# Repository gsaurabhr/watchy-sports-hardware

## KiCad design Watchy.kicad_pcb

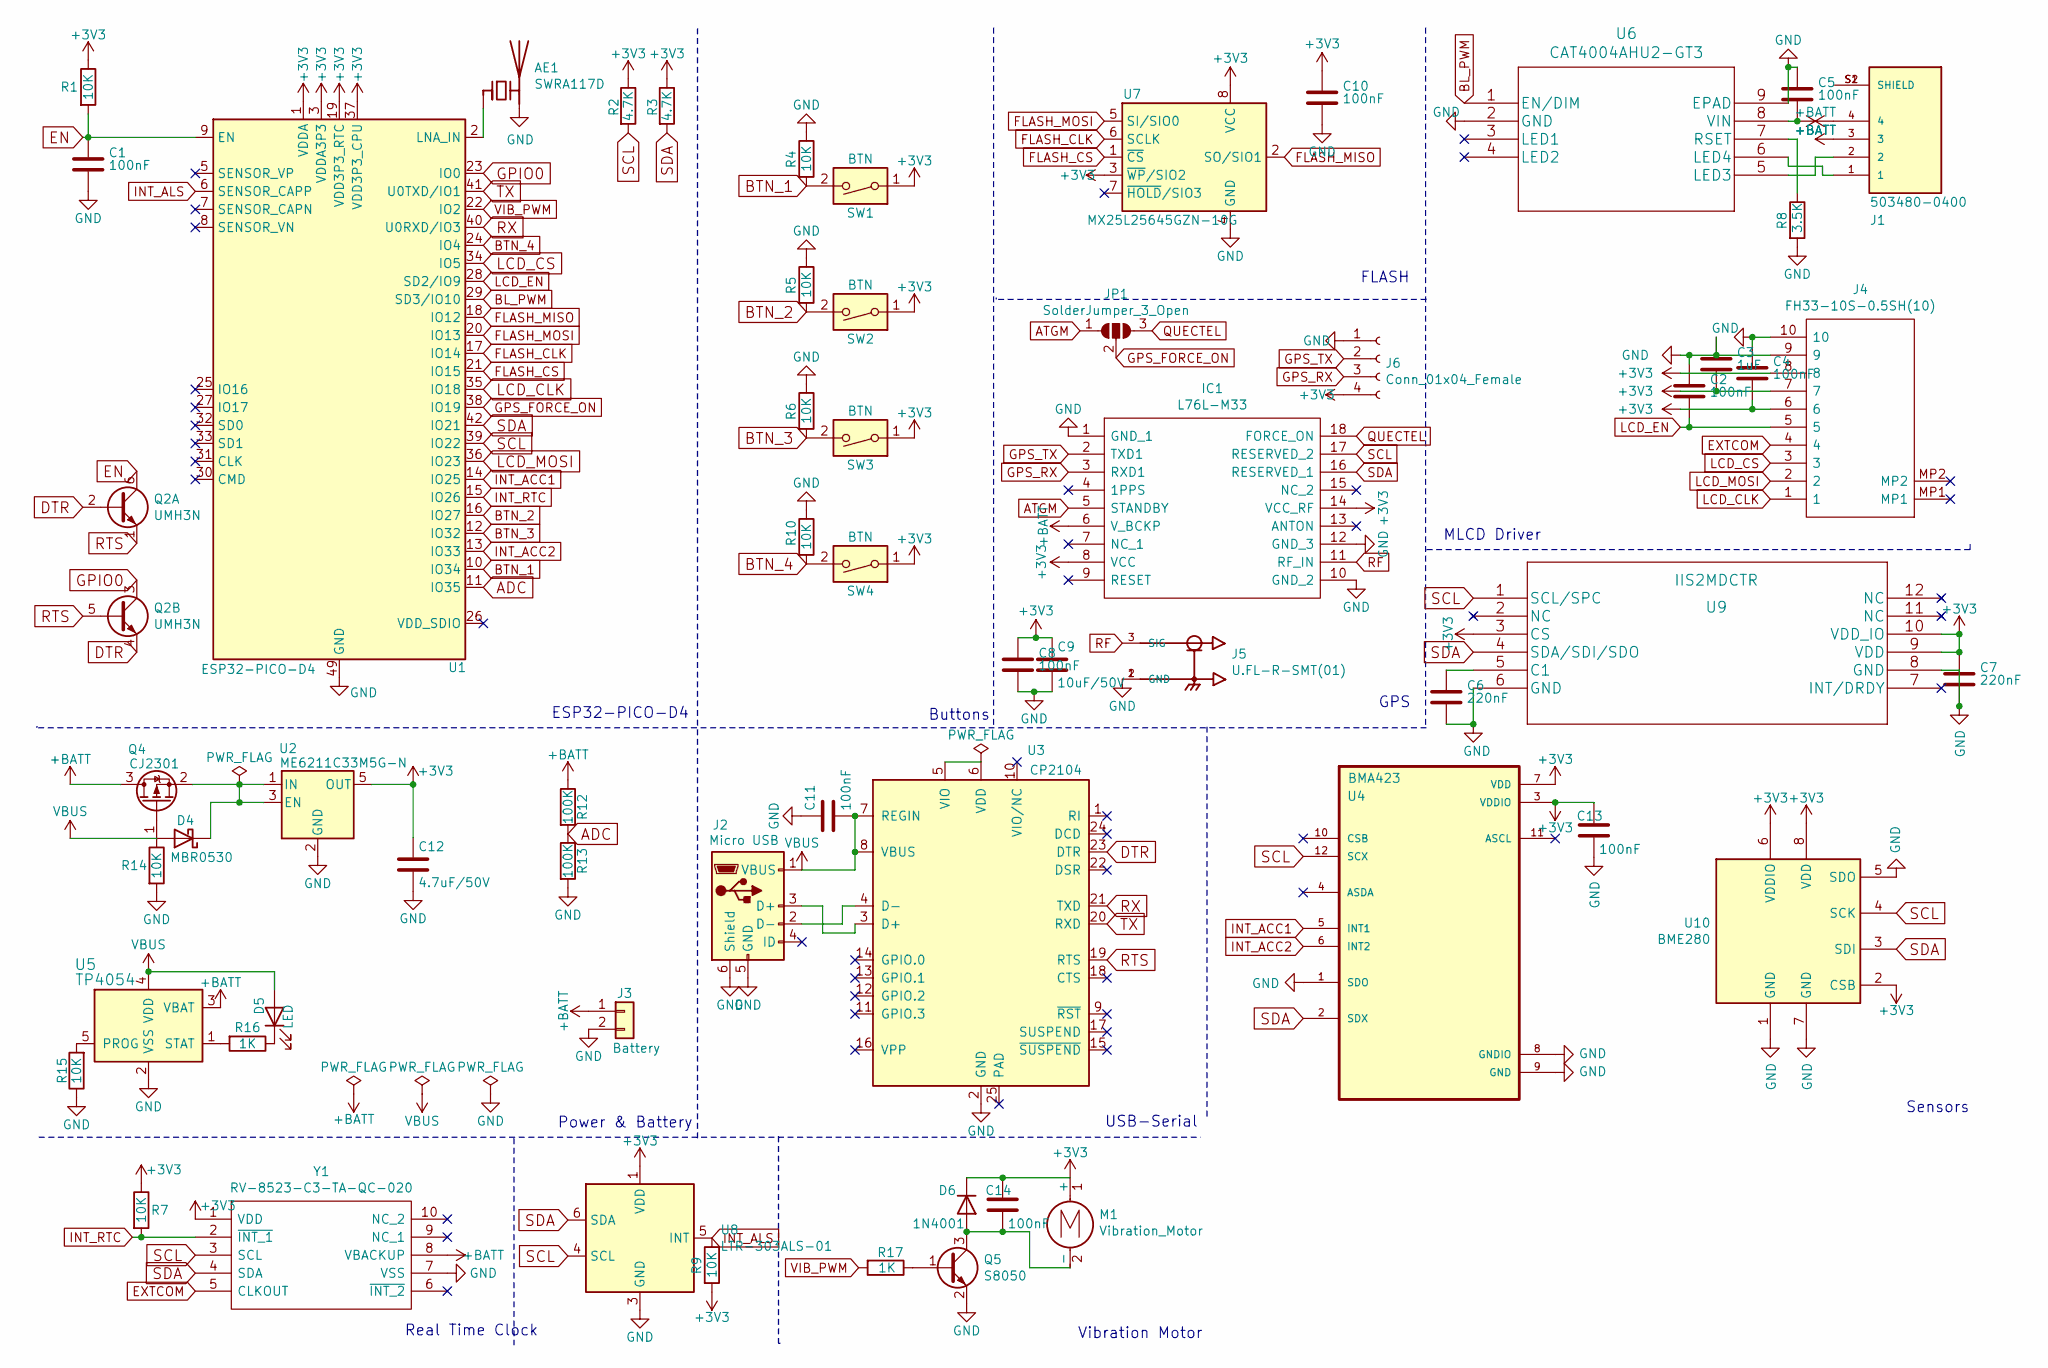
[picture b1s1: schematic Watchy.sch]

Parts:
AE1: SWRA117D
C1, C2, C4, C5, C8, C10, C11, C13, C14: 100nF; C_0603_1608Metric
C3: 1uF; C_0603_1608Metric
C6, C7: 220nF; C_0603_1608Metric
C9: 10uF/50V; C_0805_2012Metric
C12: 4.7uF/50V; C_0805
D4: MBR0530; D_SOD-123; MPN MBR0530; LCSC C77336
D5: LED; LED_0603; MPN LTST-C190KRKT; LCSC C2286
D6: 1N4001; D_SOD-123F; MPN 1N4001; LCSC C433392
IC1: L76L-M33; L76; Manufacturer_Part_Number L76L-M33; Mouser Part Number 277-L76-M33
J1: 503480-0400; MOLEX_503480-0400; MPN 503480-0400; LCSC C563965
J2: Micro USB; USB_Micro-B; MPN U-F-M5DD-Y-L; LCSC C91146
J3: Battery; 1.25T-2PWT (Molex 532610271); MPN 532610271; LCSC C189700
J4: FH33-10S-0.5SH(10); FH3310S05SH10; MPN FH33-10S-0.5SH(10); Mouser Part Number 798-FH3310S0.5SH10
J5: U.FL-R-SMT(01); HRS_U.FL-R-SMT(01); MPN U.FL-R-SMT(01); LCSC C88374
J6: Conn_01x04_Female; PinSocket_1x04_P1.00mm_Vertical
JP1: SolderJumper_3_Open; SolderJumper-3_P1.3mm_Open_Pad1.0x1.5mm
M1: Vibration_Motor; Motor_Header
Q2: UMH3N; SOT-363_SC-70-6; MPN UMH3N; LCSC C62892
Q4: CJ2301; SOT-23; MPN CJ2301; LCSC C8547
Q5: S8050; SOT-23; MPN S8050; LCSC C2146
R1, R4, R5, R6, R7, R9, R10, R14, R15: 10K; R_0402_1005Metric
R2, R3: 4.7K; R_0402_1005Metric
R8: 3.5K; R_0402_1005Metric
R12, R13: 100K; R_0402_1005Metric
R16, R17: 1K; R_0402_1005Metric
SW1, SW2, SW3, SW4: BTN; K2-1114SA-A4SW-06; MPN K2-1114SA-A4SW-06; LCSC C136662
U1: ESP32-PICO-D4; QFN-48-1EP_7x7mm_Pitch0.5mm; MPN ESP32-PICO-D4; LCSC C193707
U2: ME6211C33M5G-N; SOT-23-5; MPN ME6211C33M5G-N; LCSC C82942
U3: CP2104; QFN-24-1EP_4x4mm_Pitch0.5mm; MPN CP2104-F03-GM; LCSC C430013
U4: BMA423; LGA-12_2x2mm_Pitch0.5mm; MPN BMA423; LCSC C189517
U5: TP4054; SOT-23-5; MPN TP4054; LCSC C32574
U6: CAT4004AHU2-GT3; MPN CAT4004AHU2-GT3; LCSC C184239
U7: MX25L25645GZN-10G; WSON-8-1EP_6x5mm_P1.27mm_EP3.4x4mm; MPN MX25L25645GZN-10G; LCSC C2802981
U8: LTR-303ALS-01; Lite-On_LTR-303ALS-01; MPN LTR-303ALS-01; LCSC C364577
U9: IIS2MDCTR; MPN IIS2MDCTR; LCSC C2655002
U10: BME280; Bosch_LGA-8_2.5x2.5mm_P0.65mm_ClockwisePinNumbering; MPN BME280; LCSC C92489
Y1: RV-8523-C3-TA-QC-020; RV8523C3TAQC020; MPN RV-8523-C3-TA-QC-020; Mouser Part Number N/A

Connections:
+3V3: C3.2, C4.2, C7.1, C8.1, C9.1, C10.1, C12.1, C13.1, C14.1, D6.1 (K), IC1.8 (VCC), IC1.14 (VCC_RF), J4.6, J4.7, J4.8, J6.4, M1.1 (+), R1.1, R2.1, R3.1, R7.1, R9.2, SW1.1, SW2.1, SW3.1, SW4.1, U1.1 (VDDA), U1.3 (VDDA3P3), U1.4 (VDDA3P3), U1.19 (VDD3P3_RTC), U1.37 (VDD3P3_CPU), U1.43 (VDDA), U1.46 (VDDA), U2.5 (OUT), U4.3 (VDDIO), U4.7 (VDD), U7.3 (~WP~/SIO2), U7.8 (VCC), U8.1 (VDD), U9.3 (CS), U9.9 (VDD), U9.10 (VDD_IO), U10.2 (CSB), U10.6 (VDDIO), U10.8 (VDD), Y1.1 (VDD)
+BATT: C5.2, IC1.6 (V_BCKP), J1.3, J1.4, J3.1, Q4.3 (D), R12.1, U5.3 (VBAT), U6.8 (VIN), Y1.8 (VBACKUP)
ADC: R12.2, R13.1, U1.11 (IO35)
ATGM: IC1.5 (STANDBY), JP1.1 (A)
BL_PWM: U1.29 (SD3/IO10), U6.1 (EN/DIM)
BTN_1: R4.2, SW1.2, U1.10 (IO34)
BTN_2: R5.2, SW2.2, U1.16 (IO27)
BTN_3: R6.2, SW3.2, U1.12 (IO32)
BTN_4: R10.2, SW4.2, U1.24 (IO4)
DTR: Q2.2 (B1), Q2.4 (E2), U3.23 (DTR)
EN: C1.1, Q2.6 (C1), R1.2, U1.9 (EN)
EXTCOM: J4.4, Y1.5 (CLKOUT)
FLASH_CLK: U1.17 (IO14), U7.6 (SCLK)
FLASH_CS: U1.21 (IO15), U7.1 (~CS)
FLASH_MISO: U1.18 (IO12), U7.2 (SO/SIO1)
FLASH_MOSI: U1.20 (IO13), U7.5 (SI/SIO0)
GND: AE1.2 (PCB_Trace), C1.2, C2.1, C3.1, C4.1, C5.1, C6.2, C7.2, C8.2, C9.2, C10.2, C11.1, C12.2, C13.2, IC1.1 (GND_1), IC1.10 (GND_2), IC1.12 (GND_3), J2.5 (GND), J2.6 (Shield), J3.2, J4.9, J4.10, J5.1 (GND), J5.2 (GND), J6.1, Q5.2 (E), R4.1, R5.1, R6.1, R8.2, R10.1, R13.2, R14.2, R15.1, U1.49 (GND), U2.2 (GND), U3.2 (GND), U4.1 (SDO), U4.8 (GNDIO), U4.9 (GND), U5.2 (VSS), U6.2 (GND), U6.9 (EPAD), U7.4 (GND), U7.9 (GND), U8.3 (GND), U9.6 (GND), U9.8 (GND), U10.1 (GND), U10.5 (SDO), U10.7 (GND), Y1.7 (VSS)
GPIO0: Q2.3 (C2), U1.23 (IO0)
GPS_FORCE_ON: JP1.2 (C), U1.38 (IO19)
GPS_RX: IC1.3 (RXD1), J6.3
GPS_TX: IC1.2 (TXD1), J6.2
INT_ACC1: U1.14 (IO25), U4.5 (INT1)
INT_ACC2: U1.13 (IO33), U4.6 (INT2)
INT_ALS: R9.1, U1.6 (SENSOR_CAPP), U8.5 (INT)
INT_RTC: R7.2, U1.15 (IO26), Y1.2 (~INT_1)
LCD_CLK: J4.1, U1.35 (IO18)
LCD_CS: J4.3, U1.34 (IO5)
LCD_EN: C2.2, J4.5, U1.28 (SD2/IO9)
LCD_MOSI: J4.2, U1.36 (IO23)
unnamed: AE1.1 (FEED), U1.2 (LNA_IN)
unnamed: C6.1, U9.5 (C1)
unnamed: C14.2, D6.2 (A), M1.2 (-), Q5.3 (C)
unnamed: D4.1 (K), Q4.2 (S), U2.1 (IN), U2.3 (EN)
unnamed: D5.1 (K), R16.1
unnamed: J1.1, U6.6 (LED4)
unnamed: J1.2, U6.5 (LED3)
unnamed: J1.S1 (SHIELD), J1.S2 (SHIELD)
unnamed: J2.2 (D-), U3.4 (D-)
unnamed: J2.3 (D+), U3.3 (D+)
unnamed: Q5.1 (B), R17.1
unnamed: R8.1, U6.7 (RSET)
unnamed: R15.2, U5.5 (PROG)
unnamed: R16.2, U5.1 (STAT)
unnamed: U3.5 (VIO), U3.6 (VDD)
QUECTEL: IC1.18 (FORCE_ON), JP1.3 (B)
RF: IC1.11 (RF_IN), J5.3 (SIG)
RTS: Q2.1 (E1), Q2.5 (B2), U3.19 (RTS)
RX: U1.40 (U0RXD/IO3), U3.21 (TXD)
SCL: IC1.17 (RESERVED_2), R2.2, U1.39 (IO22), U4.12 (SCX), U8.4 (SCL), U9.1 (SCL/SPC), U10.4 (SCK), Y1.3 (SCL)
SDA: IC1.16 (RESERVED_1), R3.2, U1.42 (IO21), U4.2 (SDX), U8.6 (SDA), U9.4 (SDA/SDI/SDO), U10.3 (SDI), Y1.4 (SDA)
TX: U1.41 (U0TXD/IO1), U3.20 (RXD)
VBUS: C11.2, D4.2 (A), D5.2 (A), J2.1 (VBUS), Q4.1 (G), R14.1, U3.7 (REGIN), U3.8 (VBUS), U5.4 (VDD)
VIB_PWM: R17.2, U1.22 (IO2)

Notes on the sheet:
ESP32-PICO-D4
Power & Battery
Real Time Clock
USB-Serial
Sensors
MLCD Driver
Buttons
Vibration Motor
GPS
FLASH

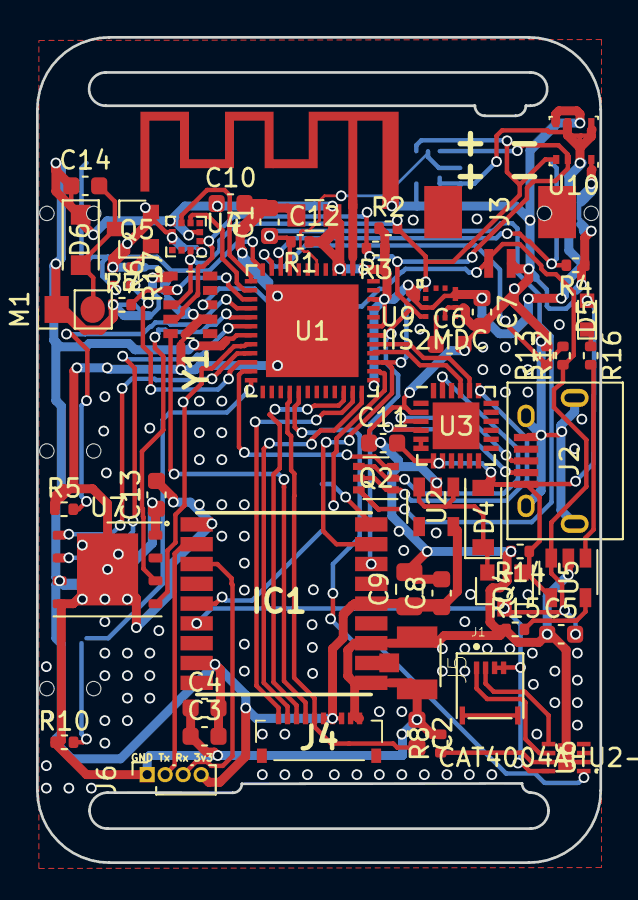
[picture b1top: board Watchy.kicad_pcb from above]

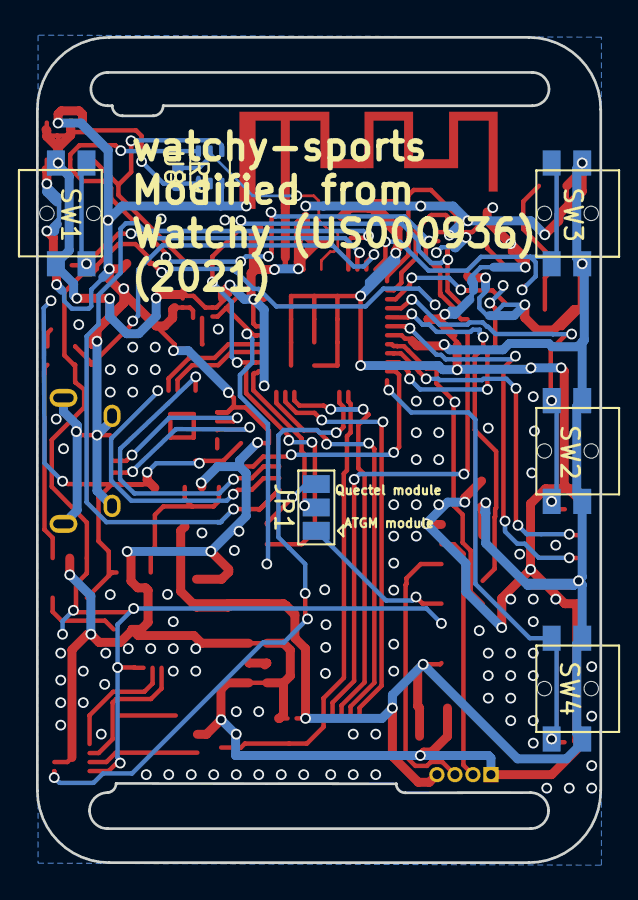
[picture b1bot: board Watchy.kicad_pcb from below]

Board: 2 copper layers, 31.3 x 45.8 mm, 61 parts (7 on the bottom side), 53 nets.

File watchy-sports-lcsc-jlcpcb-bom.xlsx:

Reference | Quantity | Value | Footprint | LCSC | MPN | LCSC Alt | Manufacturer_Name | Mouser Part Number
C1 C2 C4 C5 C8 C10 C11 C13 C14 | 9 | 100nF | Capacitor_SMD:C_0603_1608Metric
C12 | 1 | 4.7uF/50V | Capacitors_SMD:C_0805
C3 | 1 | 1uF | Capacitor_SMD:C_0603_1608Metric
C6 C7 | 2 | 220nF | Capacitor_SMD:C_0603_1608Metric
C9 | 1 | 10uF/50V | Capacitor_SMD:C_0805_2012Metric
D4 | 1 | MBR0530 | Diodes_SMD:D_SOD-123 | C77336 | MBR0530
D5 | 1 | LED | LEDs:LED_0603 | C2286 | LTST-C190KRKT
D6 | 1 | 1N4001 | Diodes_SMD:D_SOD-123F | C433392 | 1N4001
IC1 | 1 | L76L-M33 | Watchy:L76 | C2649477 | L76L-M33 | C90770 | Quectel | 277-L76-M33
J1 | 1 | 503480-0400 | Watchy:MOLEX_503480-0400 | C563965 | 503480-0400 |  | Molex, LLC
J2 | 1 | Micro USB | Watchy:USB_Micro-B | C91146 | U-F-M5DD-Y-L | C145792
J3 | 1 | Battery | Watchy:1.25T-2PWT (Molex 532610271) | C189700 | 532610271
J4 | 1 | FH33-10S-0.5SH(10) | Watchy:FH3310S05SH10 |  | FH33-10S-0.5SH(10) |  | Hirose | 798-FH3310S0.5SH10
J5 | 1 | U.FL-R-SMT(01) | Watchy:HRS_U.FL-R-SMT(01) | C88374 | U.FL-R-SMT(01) |  | Hirose
Q2 | 1 | UMH3N | TO_SOT_Packages_SMD:SOT-363_SC-70-6 | C62892 | UMH3N
Q4 | 1 | CJ2301 | TO_SOT_Packages_SMD:SOT-23 | C8547 | CJ2301
Q5 | 1 | S8050 | TO_SOT_Packages_SMD:SOT-23 | C2146 | S8050
R1 R4 R5 R6 R7 R9 R10 R14 R15 | 9 | 10K | Resistor_SMD:R_0402_1005Metric
R12 R13 | 2 | 100K | Resistor_SMD:R_0402_1005Metric
R16 R17 | 2 | 1K | Resistor_SMD:R_0402_1005Metric
R2 R3 | 2 | 4.7K | Resistor_SMD:R_0402_1005Metric
R8 | 1 | 3.5K | Resistor_SMD:R_0402_1005Metric
SW1 SW2 SW3 SW4 | 4 | BTN | Watchy:K2-1114SA-A4SW-06 | C136662 | K2-1114SA-A4SW-06
U1 | 1 | ESP32-PICO-D4 | Housings_DFN_QFN:QFN-48-1EP_7x7mm_Pitch0.5mm | C193707 | ESP32-PICO-D4
U10 | 1 | BME280 | Package_LGA:Bosch_LGA-8_2.5x2.5mm_P0.65mm_ClockwisePinNumbering | C92489 | BME280
U2 | 1 | ME6211C33M5G-N | TO_SOT_Packages_SMD:SOT-23-5 | C82942 | ME6211C33M5G-N
U3 | 1 | CP2104 | Housings_DFN_QFN:QFN-24-1EP_4x4mm_Pitch0.5mm | C430013 | CP2104-F03-GM
U4 | 1 | BMA423 | Housings_LGA:LGA-12_2x2mm_Pitch0.5mm | C189517 | BMA423 |  | Bosch Sensortec
U5 | 1 | TP4054 | TO_SOT_Packages_SMD:SOT-23-5 | C32574 | TP4054
U6 | 1 | CAT4004AHU2-GT3 | Watchy:CAT4004AHU2-GT3 | C184239 | CAT4004AHU2-GT3
U7 | 1 | MX25L25645GZN-10G | Package_SON:WSON-8-1EP_6x5mm_P1.27mm_EP3.4x4mm | C2802981 | MX25L25645GZN-10G
U8 | 1 | LTR-303ALS-01 | OptoDevice:Lite-On_LTR-303ALS-01 | C364577 | LTR-303ALS-01
U9 | 1 | IIS2MDCTR | Watchy:IIS2MDCTR | C2655002 | IIS2MDCTR
Y1 | 1 | RV-8523-C3-TA-QC-020 | Watchy:RV8523C3TAQC020 |  | RV-8523-C3-TA-QC-020 |  | Micro Crystal AG | N/A

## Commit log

2021-04-25 added or replaced parts and altered borad outline
2021-06-02 version 0 production
2021-07-26 v0 PCBWay final version
